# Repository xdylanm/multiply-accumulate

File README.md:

# Multiply Accumulate

A 4HP module with a four-quadrant multiplier.

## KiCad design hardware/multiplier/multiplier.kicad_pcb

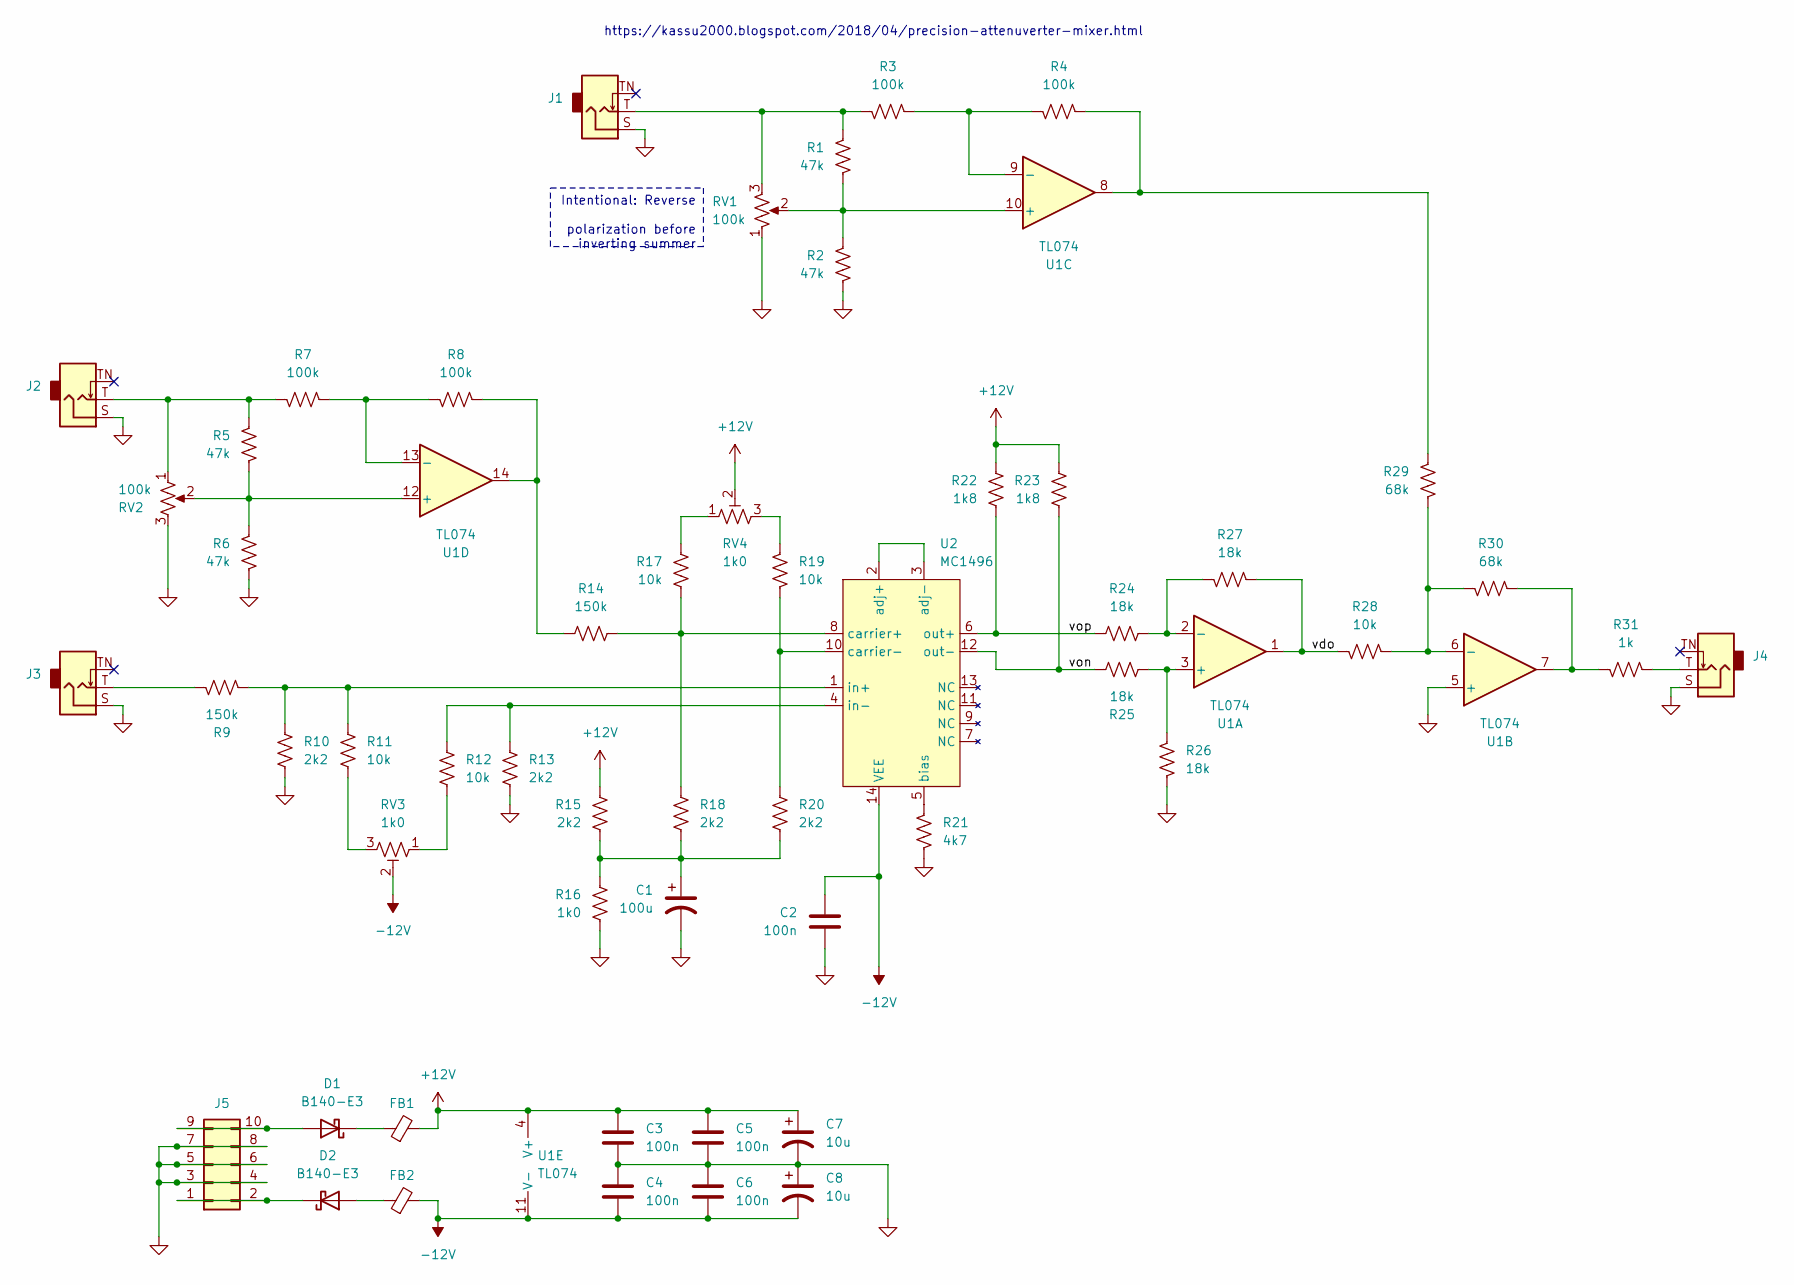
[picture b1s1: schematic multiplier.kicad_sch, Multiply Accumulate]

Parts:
C1: 100u; CP_Radial_D5.0mm_P2.00mm
C2, C3, C4, C5, C6: 100n; C_0805_2012Metric_Pad1.18x1.45mm_HandSolder
C7, C8: 10u; CP_Radial_D5.0mm_P2.00mm
D1, D2: B140-E3; D_SMA
FB1, FB2: FerriteBead_Small; L_0805_2012Metric_Pad1.05x1.20mm_HandSolder
J1, J2, J3, J4: AudioJack2_SwitchT; Jack_3.5mm_QingPu_WQP-PJ301M-12_Vertical_Slim
J5: Conn_02x05_Odd_Even; IDC-Header_2x05_P2.54mm_Vertical
R1, R2, R5, R6: 47k; R_0805_2012Metric_Pad1.20x1.40mm_HandSolder
R3, R4, R7, R8: 100k; R_0805_2012Metric_Pad1.20x1.40mm_HandSolder
R9, R14: 150k; R_0805_2012Metric_Pad1.20x1.40mm_HandSolder
R10, R13, R15, R18, R20: 2k2; R_0805_2012Metric_Pad1.20x1.40mm_HandSolder
R11, R12, R17, R19, R28: 10k; R_0805_2012Metric_Pad1.20x1.40mm_HandSolder
R16: 1k0; R_0805_2012Metric_Pad1.20x1.40mm_HandSolder
R21: 4k7; R_0805_2012Metric_Pad1.20x1.40mm_HandSolder
R22, R23: 1k8; R_0805_2012Metric_Pad1.20x1.40mm_HandSolder
R24, R25, R26, R27: 18k; R_0805_2012Metric_Pad1.20x1.40mm_HandSolder
R29, R30: 68k; R_0805_2012Metric_Pad1.20x1.40mm_HandSolder
R31: 1k; R_0805_2012Metric_Pad1.20x1.40mm_HandSolder
RV1, RV2: 100k; Potentiometer_Bourns_PTV09A-1_Single_Vertical_thin
RV3, RV4: 1k0; Bourns_3314J
U1: TL074; SOIC-14_3.9x8.7mm_P1.27mm
U2: MC1496; SOIC-14_3.9x8.7mm_P1.27mm

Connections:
+12V: C3.1, C5.1, C7.1, FB1.2, R15.1, R22.1, R23.1, RV4.2, U1.4 (V+)
-12V: C2.1, C4.2, C6.2, C8.2, FB2.2, RV3.2, U1.11 (V-), U2.14 (VEE)
/vdo: R27.2, R28.1, U1.1
/von: R23.2, R25.1, U2.12 (out-)
/vop: R22.2, R24.1, U2.6 (out+)
GND: C1.2, C2.2, C3.2, C4.1, C5.2, C6.1, C7.2, C8.1, J1.S, J2.S, J3.S, J4.S, J5.3, J5.4, J5.5, J5.6, J5.7, J5.8, R2.1, R6.1, R10.1, R13.1, R16.2, R21.2, R26.2, RV1.1, RV2.3, U1.5 (+)
unnamed: C1.1, R15.2, R16.1, R18.1, R20.1
unnamed: D1.2 (A), J5.9, J5.10
unnamed: D1.1 (K), FB1.1
unnamed: D2.2 (A), FB2.1
unnamed: D2.1 (K), J5.1, J5.2
unnamed: J1.T, R1.2, R3.1, RV1.3
unnamed: J2.T, R5.2, R7.1, RV2.1
unnamed: J3.T, R9.1
unnamed: J4.T, R31.2
unnamed: R11.1, RV3.3
unnamed: R12.1, RV3.1
unnamed: R8.2, R14.1, U1.14
unnamed: R17.1, RV4.1
unnamed: R19.1, RV4.3
unnamed: R4.2, R29.2, U1.8
unnamed: R30.2, R31.1, U1.7
unnamed: R25.2, R26.1, U1.3 (+)
unnamed: R24.2, R27.1, U1.2 (-)
unnamed: R28.2, R29.1, R30.1, U1.6 (-)
unnamed: R1.1, R2.2, RV1.2, U1.10 (+)
unnamed: R3.2, R4.1, U1.9 (-)
unnamed: R5.1, R6.2, RV2.2, U1.12 (+)
unnamed: R7.2, R8.1, U1.13 (-)
unnamed: U2.2 (adj+), U2.3 (adj-)
unnamed: R21.1, U2.5 (bias)
unnamed: R14.2, R17.2, R18.2, U2.8 (carrier+)
unnamed: R19.2, R20.2, U2.10 (carrier-)
unnamed: R9.2, R10.2, R11.2, U2.1 (in+)
unnamed: R12.2, R13.2, U2.4 (in-)

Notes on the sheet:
https://kassu2000.blogspot.com/2018/04/precision-attenuverter-mixer.html
Intentional: Reverse polarization before inverting summer

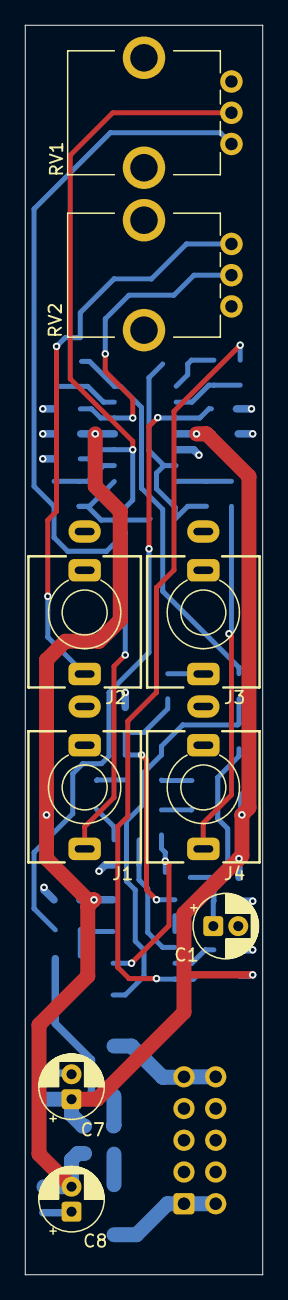
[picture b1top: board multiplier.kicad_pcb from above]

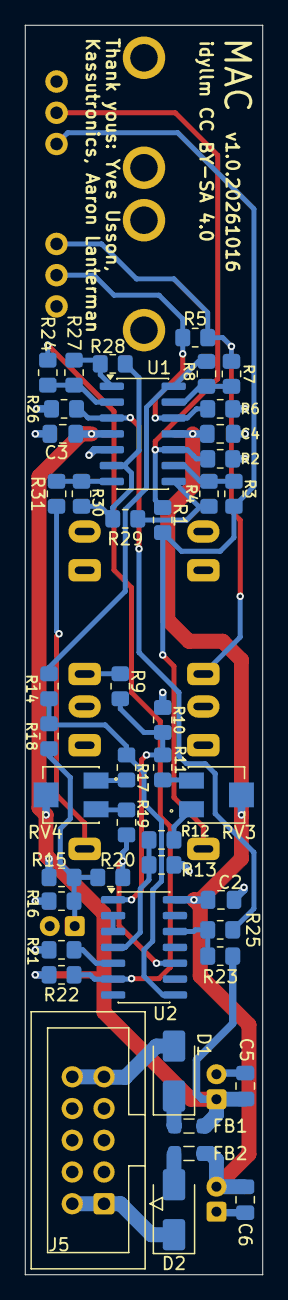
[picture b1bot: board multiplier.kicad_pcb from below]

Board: 4 copper layers, 19.0 x 100.0 mm, 54 parts (45 on the bottom side), 35 nets.

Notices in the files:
hardware/multiplier/multiplier.kicad_pcb:
idyllm CC BY-SA 4.0
hardware/multiplier/multiplier.kicad_sch:
CC BY-SA 4.0
